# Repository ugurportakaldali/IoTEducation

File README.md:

# IoT Eğitimi

Bu proje, eğitmenliğini üstlendiğim, 10 hafta süren eğitim kapsamında yapılan çalışmaları içermektedir.

Eğitim süresince IoT portalı oluşturmak hedeflendi ve bu hedef doğrultusunda 4 farklı disiplin ele alındı :
- Arduino Programlama
- Server Yazılımı
- PCB Tasarımı
- 3D Tasarım

## Proje Yapısı

[Web](https://github.com/ugurportakaldali/IoTEducation/tree/main/Web/IoTEducation/IoTEducation.Web) projesi,
sistemde bulunan cihazların yönetimini ve cihazdan gelen verilerin incelenebildiği temel bir WebAssembly yazılımıdır. 
Verileri [API](https://github.com/ugurportakaldali/IoTEducation/tree/main/Web/IoTEducation/IoTEducation.API) projesinden sağlamaktadır.

API projesinin veri tabanı bağlantısı yapılandırma dosyası üzerinden belirlenmektedir.
```json
  "ConnectionStrings": {
    "DataConnection": "Server=.;Initial Catalog=IoTEducation;User ID=suIoT;Password=IoT2022"
  }
```

Donanım tarafında hızlı prototipleme adına Arduino kartı kullanıldı. 
[Arduino](https://github.com/ugurportakaldali/IoTEducation/tree/main/Arduino), donanım tarafındaki yazılımı içermektedir.

Server tarafı ile yapılacak iletişim yapılandırma dosyası üzerinden belirlenmektedir.
```c
#define WIFI_SSID     "****"
#define WIFI_PASSWORD "****"

#define SERVER_IP    "192.168.0.104"
#define SERVER_PORT  14000
```

Donanım tarafından veriler [TCPServer](https://github.com/ugurportakaldali/IoTEducation/tree/main/Web/IoTEducation/IoTEducation.TCPServer) projesi tarafından karşılanmaktadır.

Bu proje, yapılandırma dosyasında belirtilen adreste port dinlemesi yapmaktadır.
```json
  "IPAddress": "192.168.0.104",
  "Port": "14000"
```

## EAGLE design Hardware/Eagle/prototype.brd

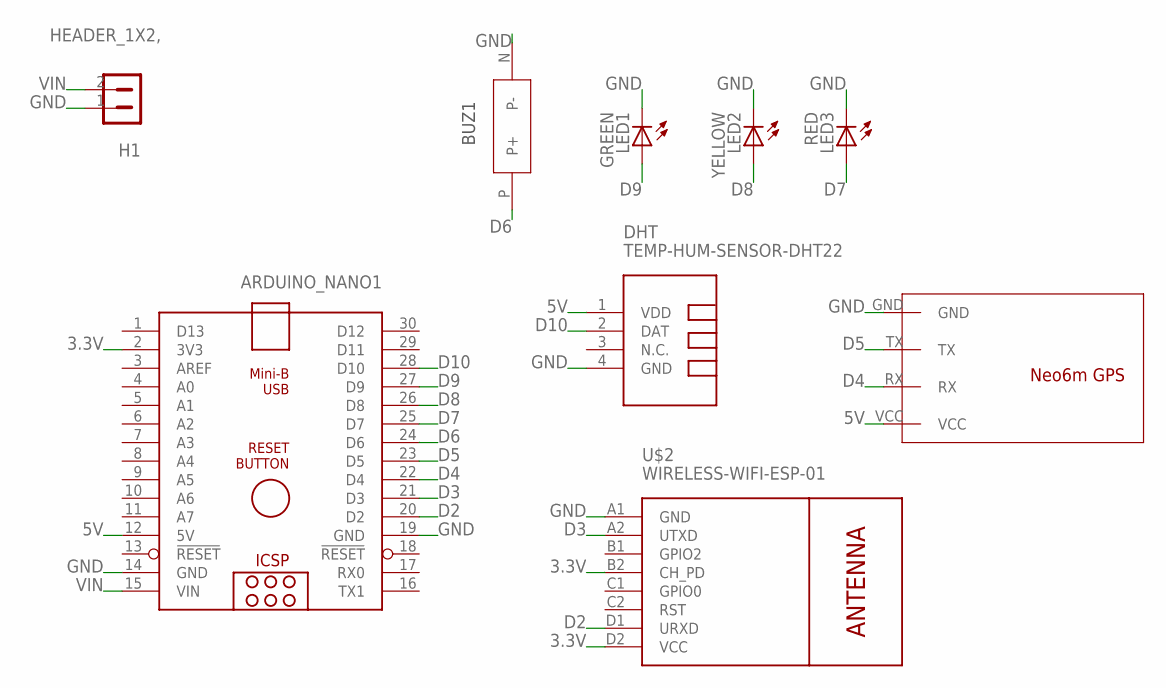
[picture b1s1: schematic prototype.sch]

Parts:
ARDUINO_NANO1: ARDUINO_NANO
BUZ1: BUZZER
DHT: TEMP-HUM-SENSOR-DHT22
H1: HEADER_1X2,; MA_2X1
LED1: GREEN; LED5MM
LED2: YELLOW; LED5MM
LED3: RED; LED5MM
U$1: NEO6M
U$2: WIRELESS-WIFI-ESP-01

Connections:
3.3V: ARDUINO_NANO1.2 (3V3), U$2.B2 (CH_PD), U$2.D2 (VCC)
5V: ARDUINO_NANO1.12 (5V), DHT.1 (VDD), U$1.VCC
D2: ARDUINO_NANO1.20 (D2), U$2.D1 (URXD)
D3: ARDUINO_NANO1.21 (D3), U$2.A2 (UTXD)
D4: ARDUINO_NANO1.22 (D4), U$1.RX
D5: ARDUINO_NANO1.23 (D5), U$1.TX
D6: ARDUINO_NANO1.24 (D6), BUZ1.P (P+)
D7: ARDUINO_NANO1.25 (D7), LED3.A
D8: ARDUINO_NANO1.26 (D8), LED2.A
D9: ARDUINO_NANO1.27 (D9), LED1.A
D10: ARDUINO_NANO1.28 (D10), DHT.2 (DAT)
GND: ARDUINO_NANO1.14 (GND), ARDUINO_NANO1.19 (GND), BUZ1.N (P-), DHT.4 (GND), H1.1, LED1.K (C), LED2.K (C), LED3.K (C), U$1.GND, U$2.A1 (GND)
VIN: ARDUINO_NANO1.15 (VIN), H1.2

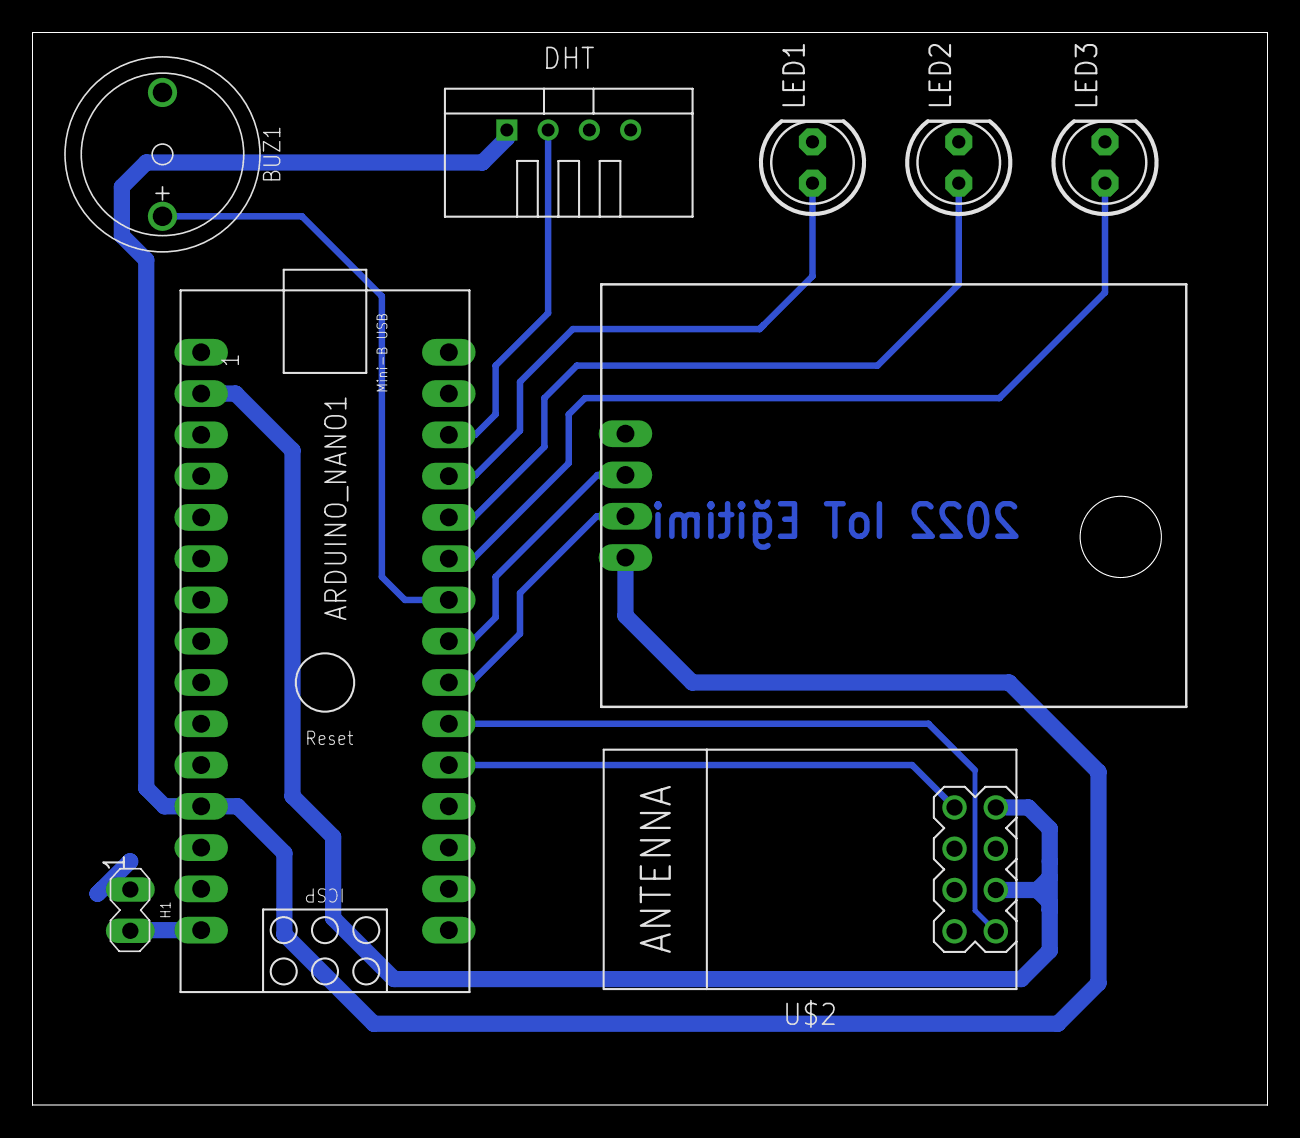
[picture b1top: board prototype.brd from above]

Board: 2 copper layers, 76.0 x 66.0 mm, 9 parts (0 on the bottom side), 13 nets.

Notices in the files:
parts and their libraries:
diy-modules: Released under the Creative Commons Attribution 4.0 International License: http://creativecommons.org/licenses/by/4.0
